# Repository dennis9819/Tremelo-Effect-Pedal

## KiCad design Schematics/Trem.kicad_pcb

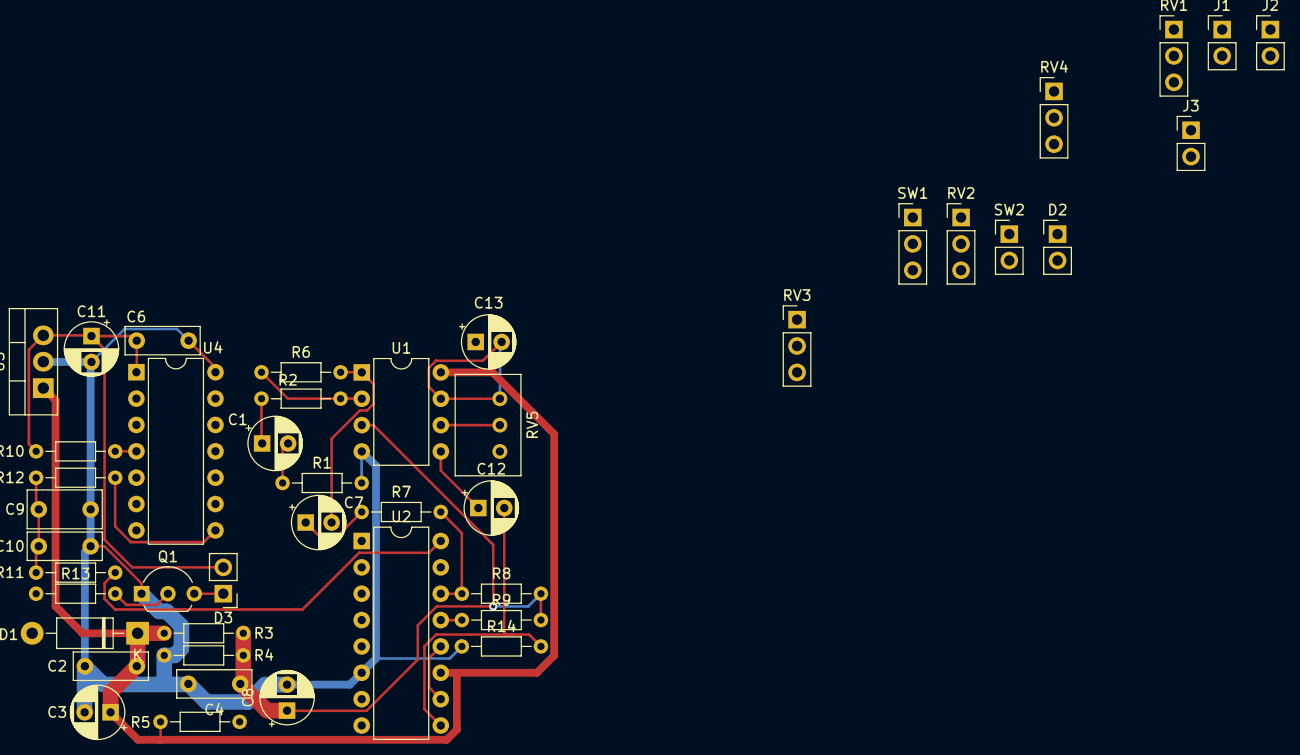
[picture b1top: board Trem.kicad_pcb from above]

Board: 2 copper layers, 44 parts (0 on the bottom side), 31 nets.

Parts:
C1, C7, C12, C13: 1uF; CP_Radial_D5.0mm_P2.50mm
C2, C4, C6, C10: 100nF; C_Rect_L7.0mm_W2.5mm_P5.00mm
C3: 100uF; CP_Radial_D5.0mm_P2.50mm
C8, C11: 47uF; CP_Radial_D5.0mm_P2.50mm
C9: 330nF; C_Rect_L7.0mm_W3.5mm_P5.00mm
D1: 1N5817; D_DO-41_SOD81_P10.16mm_Horizontal
D2: LED_ON; PinHeader_1x02_P2.54mm_Vertical
D3: LED_PULSE; PinHeader_1x02_P2.54mm_Vertical
J1: Jack-DC; PinHeader_1x02_P2.54mm_Vertical
J2, J3: AudioJack2; PinHeader_1x02_P2.54mm_Vertical
Q1: 2N4401; TO-92L_Inline_Wide
R1: 1M; R_Axial_DIN0204_L3.6mm_D1.6mm_P7.62mm_Horizontal
R2, R7, R13: 100k; R_Axial_DIN0204_L3.6mm_D1.6mm_P7.62mm_Horizontal
R3, R4: 2k2; R_Axial_DIN0204_L3.6mm_D1.6mm_P7.62mm_Horizontal
R5, R10: 10k; R_Axial_DIN0204_L3.6mm_D1.6mm_P7.62mm_Horizontal
R6: 330k; R_Axial_DIN0204_L3.6mm_D1.6mm_P7.62mm_Horizontal
R8, R9: 1k; R_Axial_DIN0204_L3.6mm_D1.6mm_P7.62mm_Horizontal
R11: 120k; R_Axial_DIN0204_L3.6mm_D1.6mm_P7.62mm_Horizontal
R12: 20k; R_Axial_DIN0204_L3.6mm_D1.6mm_P7.62mm_Horizontal
R14: 4k7; R_Axial_DIN0204_L3.6mm_D1.6mm_P7.62mm_Horizontal
RV1, RV2, RV3: 10k; PinHeader_1x03_P2.54mm_Vertical
RV4: 50k LOG; PinHeader_1x03_P2.54mm_Vertical
RV5: 20k; Potentiometer_Bourns_3299W_Vertical
SW1: SW_SPDT_MSM; PinHeader_1x03_P2.54mm_Vertical
SW2: SW_Push; PinHeader_1x02_P2.54mm_Vertical
U1: TL072; DIP-8_W7.62mm
U2: LM13700; DIP-16_W7.62mm
U3: L7805; TO-220-3_Vertical
U4: ATtiny44A-P; DIP-14_W7.62mm

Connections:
+5V: C6.1, C11.1, D3.2 (A), R10.1, RV1.1, RV2.1, RV3.1, U3.3 (OUT), U4.1 (VCC)
+9V: C2.1, C3.1, D1.1 (K), R3.1, R5.2, U1.8 (V+), U2.11 (V+), U3.1 (IN)
/VREF: C4.1, C8.1, R3.2, R4.1, R8.2, R9.2, U1.3 (+)
GND: C2.2, C3.2, C4.2, C6.2, C8.2, C9.1, C10.1, C11.2, D2.1 (K), J1.1, Q1.1 (E), R1.2, R4.2, R14.1, RV1.3, RV2.3, RV3.3, RV4.3, RV5.1, SW1.2, SW2.2, U1.4 (V-), U2.6 (V-), U3.2 (GND), U4.14 (GND)
unnamed: C1.1, R2.1
unnamed: C1.2, R1.1
unnamed: C7.1, R7.1
unnamed: C7.2, R6.2, U1.1
unnamed: C9.2, C10.2, R11.1, R12.2, R13.1
unnamed: C12.1, U1.5 (+)
unnamed: C12.2, R14.2, U2.9
unnamed: C13.1, RV4.1
unnamed: C13.2, RV5.3, U1.7
unnamed: D1.2 (A), J1.2
unnamed: D2.2 (A), R5.1
unnamed: D3.1 (K), Q1.3 (C)
unnamed: Q1.2 (B), R13.2
unnamed: R2.2, R6.1, U1.2 (-)
unnamed: R7.2, R8.1, U2.14 (+)
unnamed: R9.1, U2.13 (-)
unnamed: R10.2, U4.4 (~RESET/PB3)
unnamed: R11.2, U2.16
unnamed: R12.1, U4.8 (PA5)
unnamed: RV1.2, U4.13 (AREF/PA0)
unnamed: RV2.2, U4.12 (PA1)
unnamed: RV3.2, U4.11 (PA2)
unnamed: RV5.2, U1.6 (-)
unnamed: SW1.1, U4.6 (PA7)
unnamed: SW1.3, U4.10 (PA3)
unnamed: SW2.1, U4.3 (XTAL2/PB1)
unnamed: U2.10, U2.12

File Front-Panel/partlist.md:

# Partlist
## Case
* 1x Box Type BB (https://www.musikding.de/Alu-Gehaeuse-Typ-BB)
* 2x 3PDT Footswitch (https://www.musikding.de/3PDT-Fussschalter)
* 1x Carling 1PST Footswitch (https://www.musikding.de/Carling-1PST-Fussschalter)
* 3x LED-Bezel 5mm chrome (https://www.musikding.de/LED-Fassung-5mm-Chrom-Innenreflektor)
* 3x 5mm LED
* 1x Alpha Potentiometer 16mm 50k log (https://www.musikding.de/Alpha-Potentiometer-16mm-50k-log)
* 4x Alpha Potentiometer 16mm 10k lin (https://www.musikding.de/Alpha-Potentiometer-16mm-10k-lin)
* 1x Toggleswitch 1 pole ON-OFF-ON (https://www.musikding.de/Kippschalter-1polig-ON-OFF-ON)

## Circuit
### ICs
* 1x TL072 (https://www.reichelt.de/j-fet-operationsverstaerker-2-fach-1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
* 1x LM13700 (https://www.reichelt.de/transkonduktanzverstaerker-2-fach-di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
* 1x Attiny (https://www.reichelt.de/8-bit-attiny-avr-risc-mikrocontrolle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
* 1x L7805 (https://www.reichelt.de/spannungsregler-fest-5-v-1-5a-4-to-2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
* 1x 2N4401 (https://www.reichelt.de/bipolartransistor-npn-40v-0-6a-0-25w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

### Polarized Capacitor
* 1x 100uF 25V (https://www.reichelt.de/elko-radial-100-uf-25-v-105-c-low-es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
* 5x 1uF (https://www.reichelt.de/elko-radial-1-0-f-250-v-rm-2-5-85-c-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
* 1x 47uF 16V (https://www.reichelt.de/elko-radial-47-f-16-v-rm-2-0-85-c-20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

### Film Capacitors
* 3x 100nF (https://www.reichelt.de/mks2-pet-kondensator-100-nf-10-63-vd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
* 1x 330nF (https://www.reichelt.de/mks2-pet-kondensator-330-nf-5-63-vdc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

### Resistors
* 1x 220R 5%
* 2x 1k 1%
* 2x 2k2 1%
* 1x 4k7 1%
* 2x 10k 5%
* 1x 20k 1%
* 1x 20k TRIM
* 3x 100k 1%
* 1x 120k 1%
* 1x 160k 1%
* 1x 330k 1%
* 1x 1M 1%

### Diode
* 1x 1N5817 (Can be jumpered if required)


## Programming
* 1x ISP Programmer for AVR (https://www.fischl.de/usbasp/)

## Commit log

2022-07-18 init
2022-07-18 added structure
2022-07-18 added partlist, changed cover
2022-07-18 fixed partlist
2022-07-18 firmware
2022-07-20 new logo and updated schematics
2022-07-21 firmware update
